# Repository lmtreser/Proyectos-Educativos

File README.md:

# Proyectos Educativos

Proyectos educativos (de diversos origenes) relacionados con trabajos prácticos de las escuelas EEST N°2, EEST N°3 y EEST N°5 de la ciudad de Mar del Plata.

Los diagramas esquemáticos en su mayoría están realizados con Autodesk EAGLE (v7 o superior), y en algunos casos con KiCad (v7 o superior). Mientras que el código generalmente está basado en la API de Arduino.

La ultima versión se puede descargar desde el repositorio [en este enlace](https://github.com/lmtreser/Proyectos).

## Contenidos

- `Analogicas 44` Trabajos "Aplicaciones de Electrónica Analógica I"
- `ArduProfe` Placa entrenadora para Arduino Nano, por el prof. Alejandro Cordero
- `Difusión` Charlas, eventos y difusiones en general
- `Diseño Asistido` Trabajos de diseño de esquemas y PCBs
- `Eduqube` PocketQube educative kit, by [Innova Space](https://www.innova-space.com)
- `Entrenadora Digital` Trabajo práctico "Aplicaciones de Electrónica Digital III"
- `Internet of Things` Trabajos relacionados al IoT
- `Lenguajes Electrónicos` Trabajos "Lenguajes Electrónicos II"
- `Micro Automata` Trabajo práctico "Montaje de Proyectos Electrónicos III"
- `Pulsador de Potencia` Feria de Ciencias, trabajo interdisciplinar, extracurricular
- `Robotec` Competencia de Robótica intercolegial, trabajo interdisciplinar, extracurricular
- `Sensor de Proximidad` Trabajo práctico "Montaje de Proyectos Electrónicos III"

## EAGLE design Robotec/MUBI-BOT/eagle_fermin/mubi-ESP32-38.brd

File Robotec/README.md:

# ROBOTEC

Competencia de Robótica Institucional e Interinstitucional de Escuelas Técnicas de la ciudad de Mar del Plata para alumnos del Ciclo Básico o Superior (Tecnicatura en Electrónica).

[Sitio Web Oficial](https://robotecc.carrd.co/).

## Contenidos del repositorio

- Mubi-Bot es una serie de placas genéricas para la competencia diseñadas por el profesor Fermín Oyarburo de la E.E.S.T. N°5.

- Sigue-Lineas Tercero es un seguidor de lineas que no utiliza microcontrolador. Ideal para su utilización con el Ciclo Básico. Ha sido puesto en marcha con total éxito por el profesor Alfredo Castro de E.E.S.T. N°3.

También se encuentra disponible para su descarga una biblioteca de programación para la API de Arduino, escrita por el profesor Lucas Martín Treser de E.E.S.T. N°3 y E.E.S.T. N°5. La misma permite usar de manera simplificada los componentes más usuales de estos dispositivos. El repositorio se encuentra [aquí](https://github.com/lmtreser/Robotec).

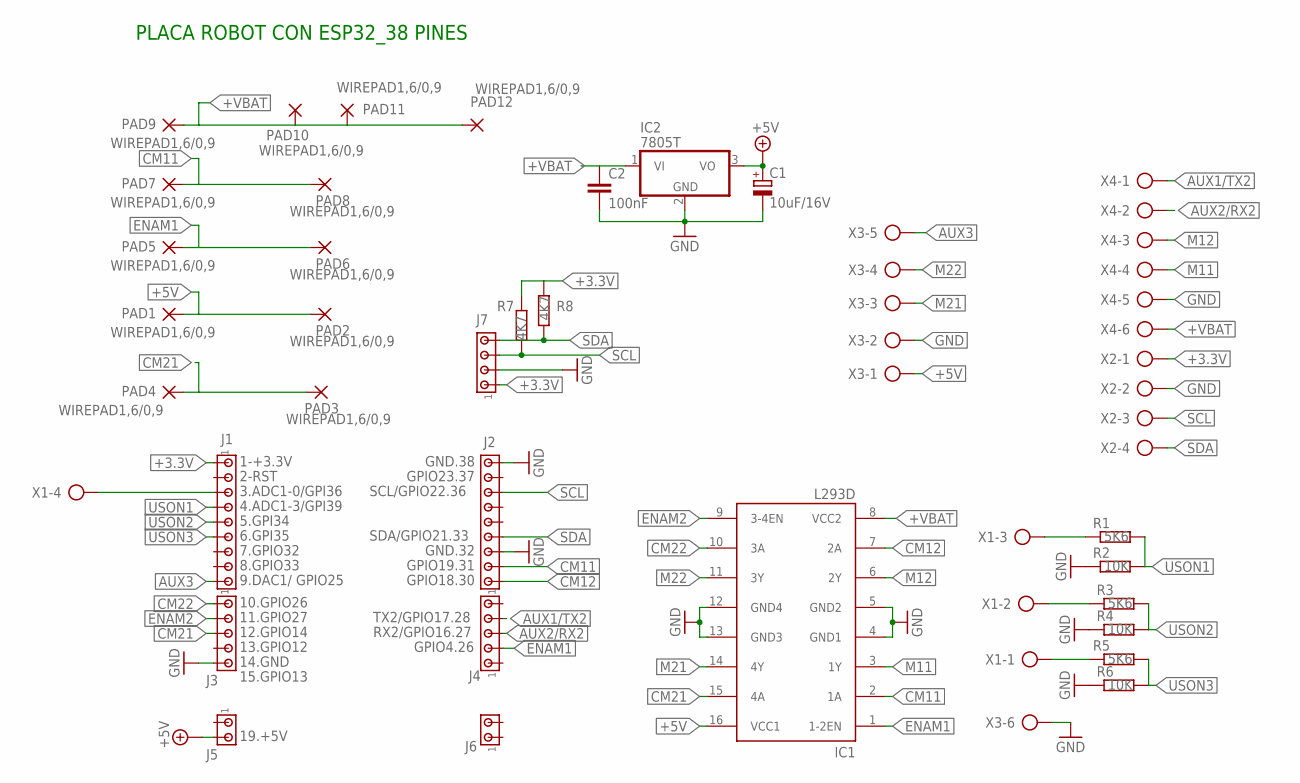
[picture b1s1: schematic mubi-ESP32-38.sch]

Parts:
C1: 10uF/16V; E2,5-6
C2: 100nF; C025-025X050
IC1: L293D; DIL16
IC2: 7805T; TO220H
J1, J2: MTA09-100; 10X09MTA
J3, J4: MTA05-100; 10X05MTA
J5, J6: MTA02-100; 10X02MTA
J7: MTA04-100; 10X04MTA
PAD1, PAD2, PAD3, PAD4, PAD5, PAD6, PAD7, PAD8, PAD9, PAD10, PAD11, PAD12: WIREPAD1,6/0,9; 1,6/0,9
R1, R3, R5: 5K6; 0204/5
R2, R4, R6: 10K; 0204/5
R7, R8: 4K7; 0207/7
X1, X2: AK500/4-H
X3, X4: AK500/6-H

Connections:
+3.3V: J1.1, J7.1, R7.2, R8.2, X2.1
+5V: C1.+, IC1.16 (VCC1), IC2.3 (VO), J5.2, PAD1.1, PAD2.1, X3.1
+VBAT: C2.1, IC1.8 (VCC2), IC2.1 (VI), PAD9.1, PAD10.1, PAD11.1, PAD12.1, X4.6
AUX1/TX2: J4.4, X4.1
AUX2/RX2: J4.3, X4.2
AUX3: J1.9, X3.5
CM11: IC1.2 (1A), J2.2, PAD7.1, PAD8.1
CM12: IC1.7 (2A), J2.1
CM21: IC1.15 (4A), J3.3, PAD3.1, PAD4.1
CM22: IC1.10 (3A), J3.1
ENAM1: IC1.1 (1-2EN), J4.2, PAD5.1, PAD6.1
ENAM2: IC1.9 (3-4EN), J3.2
GND: C1.-, C2.2, IC1.4 (GND1), IC1.5 (GND2), IC1.12 (GND4), IC1.13 (GND3), IC2.2 (GND), J2.3, J2.9, J3.5, J7.2, R2.1, R4.1, R6.1, X2.2, X3.2, X3.6, X4.5
M11: IC1.3 (1Y), X4.4
M12: IC1.6 (2Y), X4.3
M21: IC1.14 (4Y), X3.3
M22: IC1.11 (3Y), X3.4
unnamed: R1.1, X1.3
unnamed: R3.1, X1.2
unnamed: R5.1, X1.1
unnamed: J1.3, X1.4
SCL: J2.7, J7.3, R7.1, X2.3
SDA: J2.4, J7.4, R8.1, X2.4
USON1: J1.4, R1.2, R2.2
USON2: J1.5, R3.2, R4.2
USON3: J1.6, R5.2, R6.2

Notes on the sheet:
1-+3.3V
2-RST
3.ADC1-0/GPI36
4.ADC1-3/GPI39
5.GPI34
6.GPI35
7.GPIO32
8.GPIO33
9.DAC1/ GPIO25
10.GPIO26
11.GPIO27
12.GPIO14
14.GND
15.GPIO13
19.+5V
GND.38
GPIO23.37
SCL/GPIO22.36
SDA/GPIO21.33
GND.32
GPIO19.31
GPIO18.30
TX2/GPIO17.28
RX2/GPIO16.27
GPIO4.26
PLACA ROBOT CON ESP32_38 PINES
13.GPIO12

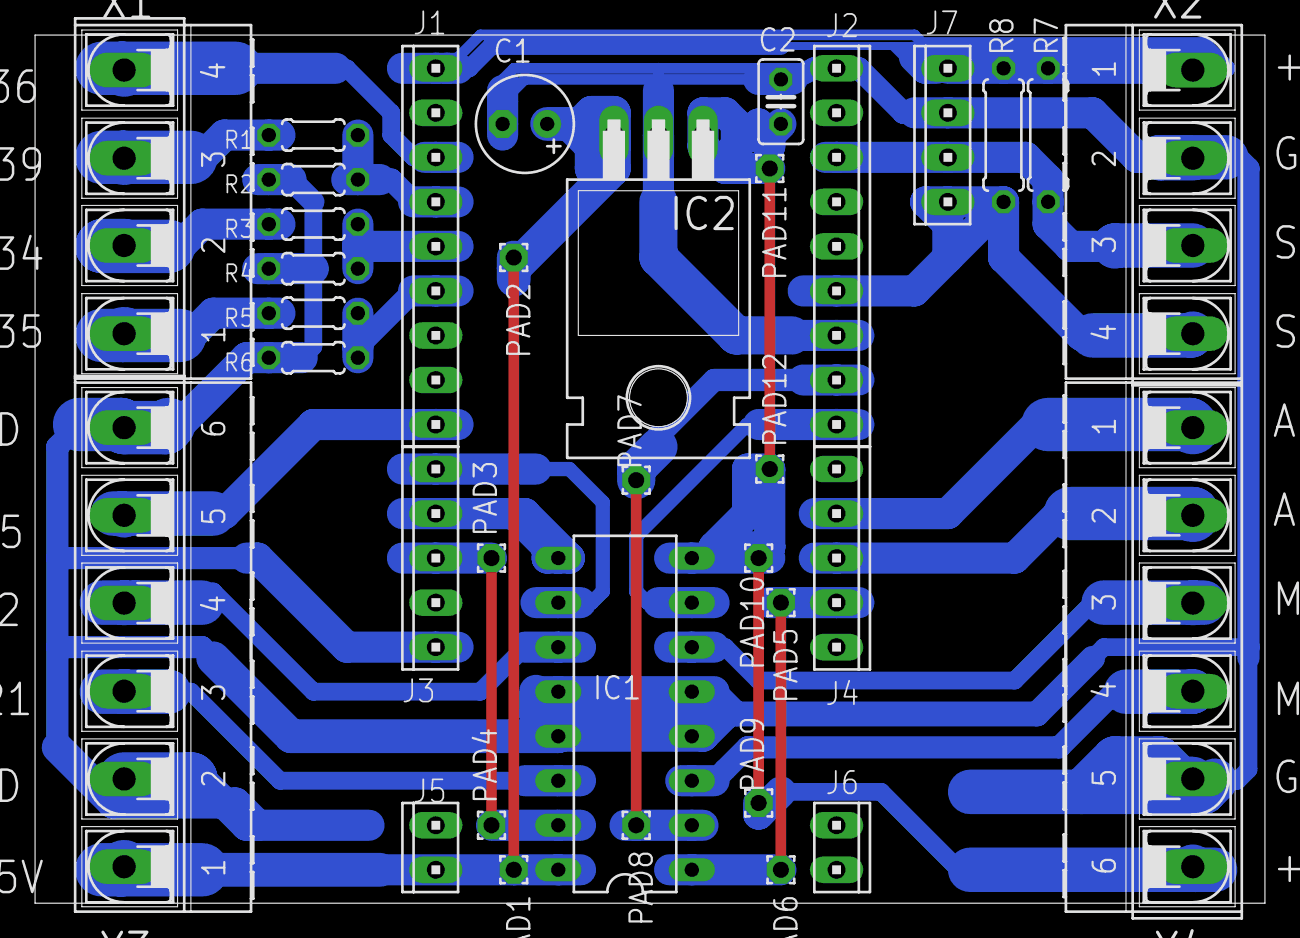
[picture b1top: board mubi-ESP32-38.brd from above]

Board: 2 copper layers, 70.2 x 49.5 mm, 35 parts (0 on the bottom side), 26 nets.

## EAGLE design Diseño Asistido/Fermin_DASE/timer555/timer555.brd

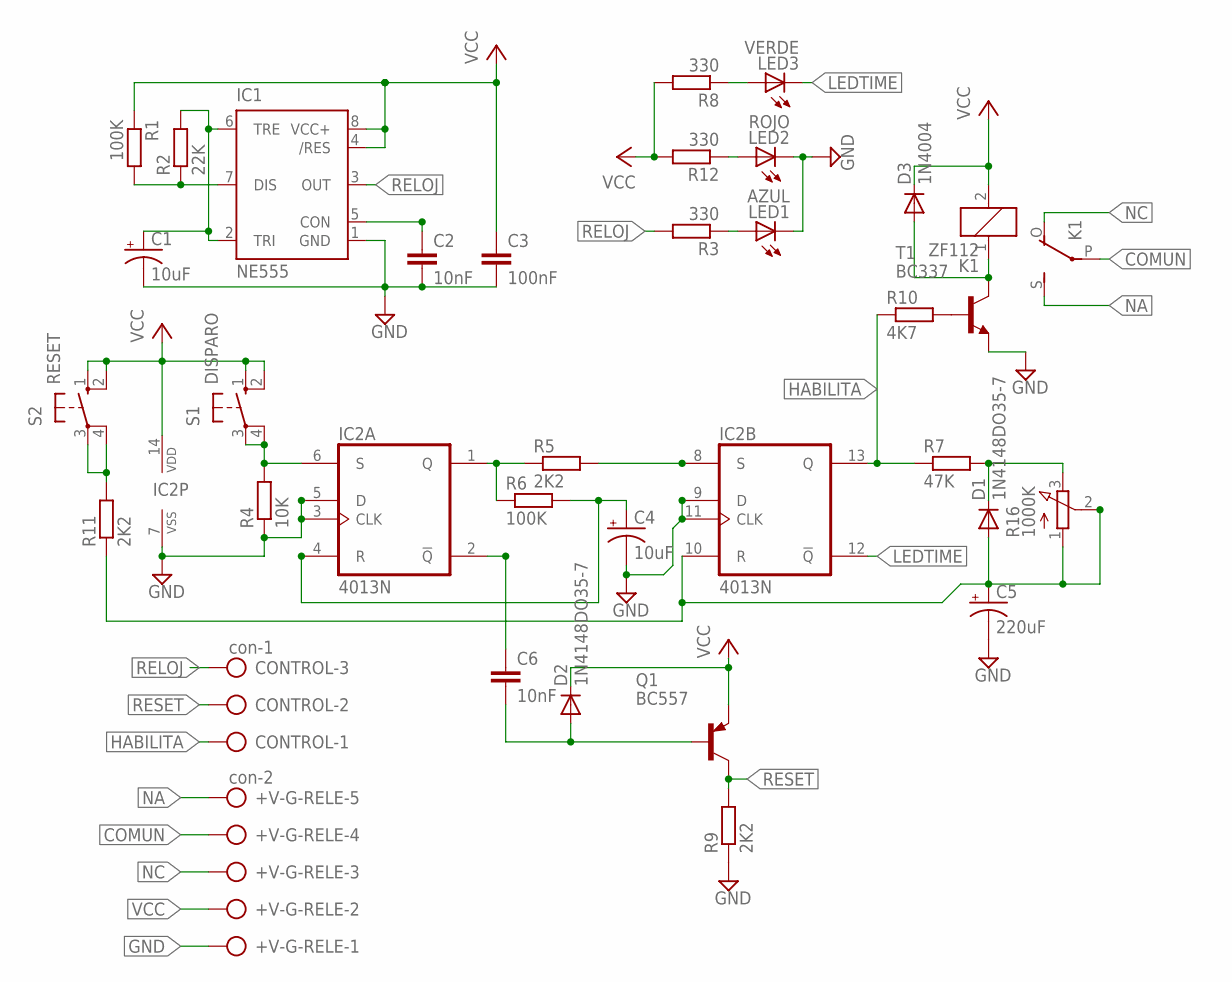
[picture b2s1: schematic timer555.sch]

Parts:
+V-G-RELE: con-2; AK500/5
C1, C4: 10uF; E2,5-5
C2, C6: 10nF; C050-025X075
C3: 100nF; C050-025X075
C5: 220uF; E3,5-8
CONTROL: con-1; AK500/3
D1, D2: 1N4148DO35-7; DO35-7
D3: 1N4004; DO41-10
IC1: NE555; DIL-08
IC2: 4013N; DIL14
K1: ZF112
LED1: AZUL; LED3MM
LED2: ROJO; LED3MM
LED3: VERDE; LED3MM
Q1: BC557; TO92-EBC
R1, R6: 100K; 0207/7
R2: 22K; 0207/7
R3, R8, R12: 330; 0207/7
R4: 10K; 0207/7
R5, R9, R11: 2K2; 0207/7
R7: 47K; 0207/7
R10: 4K7; 0207/7
R16: 1000K; 3RP/1610N
S1: DISPARO; B3F-10XX
S2: RESET; B3F-10XX
T1: BC337; TO92

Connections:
COMUN: +V-G-RELE.4, K1.P; also elsewhere on the board
GND: +V-G-RELE.1, C1.-, C2.2, C3.2, C4.-, C5.-, IC1.1 (GND), IC2.3 (CLK), IC2.5 (D), IC2.7 (VSS), IC2.9 (D), IC2.11 (CLK), LED1.K (C), LED2.K (C), R4.1, R9.1, T1.1 (E); also elsewhere on the board
HABILITA: CONTROL.1, IC2.13 (Q), R7.1, R10.1; also elsewhere on the board
LEDTIME: IC2.12 (!Q), LED3.K (C)
unnamed: D3.A, K1.1, T1.3 (C)
unnamed: IC2.1 (Q), R5.1, R6.1
unnamed: C1.+, IC1.2 (TRI), IC1.6 (TRE), R2.2
unnamed: C4.+, IC2.4 (R), R6.2
unnamed: IC1.7 (DIS), R1.2, R2.1
unnamed: C2.1, IC1.5 (CON)
unnamed: D1.C, R7.2, R16.3 (E)
unnamed: LED3.A, R8.1
unnamed: LED1.A, R3.1
unnamed: IC2.6 (S), R4.2, S1.3, S1.4 (P1)
unnamed: C5.+, D1.A, IC2.10 (R), R11.1, R16.1 (A), R16.2 (S)
unnamed: R11.2, S2.3, S2.4 (P1)
unnamed: LED2.A, R12.1
unnamed: R10.2, T1.2 (B)
unnamed: C6.1, IC2.2 (!Q)
unnamed: C6.2, D2.A, Q1.B
NA: +V-G-RELE.5, K1.S; also elsewhere on the board
RELOJ: CONTROL.3, IC1.3 (OUT), R3.2; also elsewhere on the board
RESET: CONTROL.2, Q1.C, R9.2; also elsewhere on the board
S$3: +V-G-RELE.3, K1.O
SET2: IC2.8 (S), R5.2
VCC: +V-G-RELE.2, C3.1, D2.C, D3.C, IC1.4 (/RES), IC1.8 (VCC+), IC2.14 (VDD), K1.2, Q1.E, R1.1, R8.2, R12.2, S1.1 (S), S1.2 (S1), S2.1 (S), S2.2 (S1); also elsewhere on the board

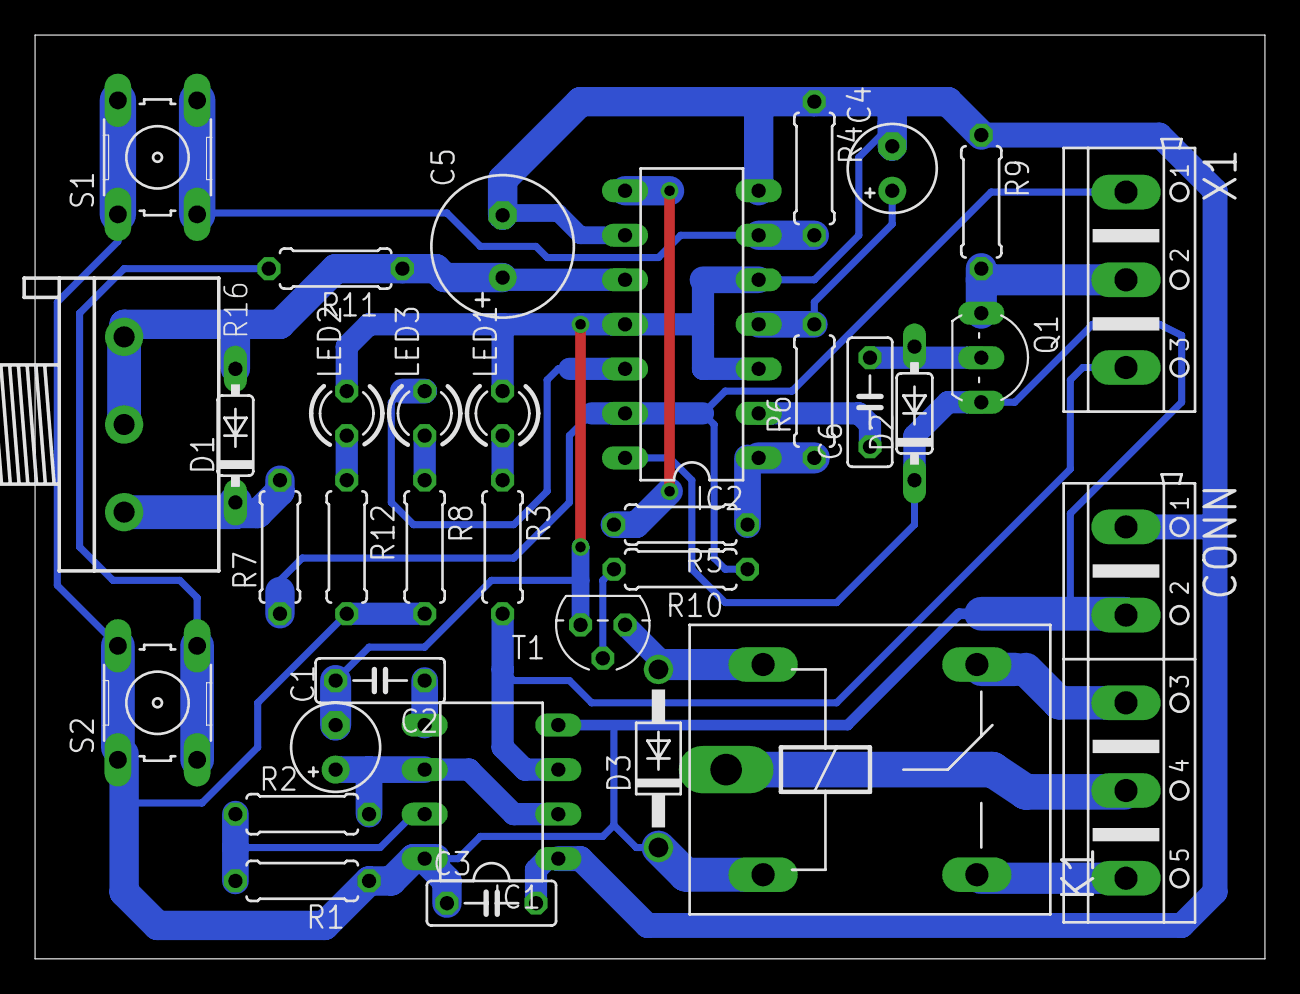
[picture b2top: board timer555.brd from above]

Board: 2 copper layers, 70.2 x 52.7 mm, 34 parts (0 on the bottom side), 25 nets.

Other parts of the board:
CONN: AK500/5
X1: AK500/3

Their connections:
COMUN: CONN.4; also elsewhere on the board
GND: CONN.1; also elsewhere on the board
HABILITA: X1.1; also elsewhere on the board
NA: CONN.5; also elsewhere on the board
RELOJ: X1.3; also elsewhere on the board
RESET: X1.2; also elsewhere on the board
VCC: CONN.2; also elsewhere on the board

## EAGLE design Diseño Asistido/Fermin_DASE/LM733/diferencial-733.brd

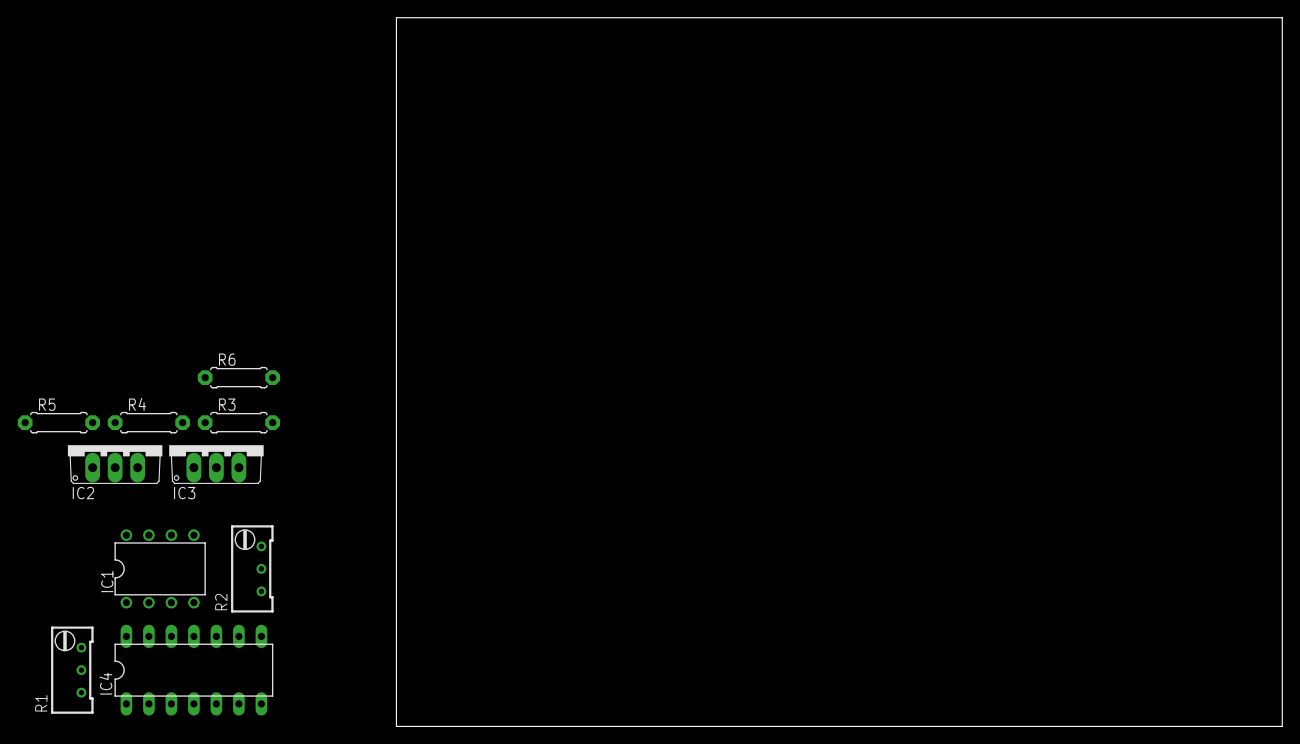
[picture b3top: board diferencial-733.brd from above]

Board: 2 copper layers, 100.0 x 80.0 mm, 10 parts (0 on the bottom side), 3 nets, no tracks yet.

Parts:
IC1: LM555N; DIL08
IC2: 7805TV; TO220V
IC3: MC79M15BT; TO220V
IC4: 7400N; DIL14
R1, R2: RTRIM64W
R3, R4, R5, R6: 0207/7

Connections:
GND: IC1.1, R4.1, R5.1
unnamed: IC4.14, R4.2
unnamed: IC4.7, R5.2

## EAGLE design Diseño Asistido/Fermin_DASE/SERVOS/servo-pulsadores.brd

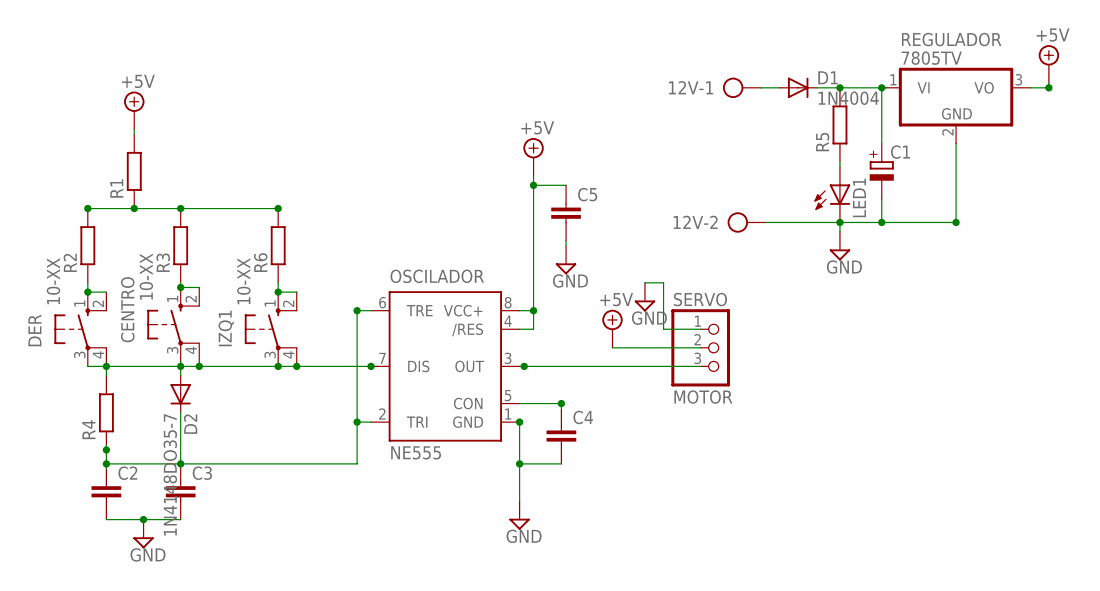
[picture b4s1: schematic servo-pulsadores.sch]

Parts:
12V: AK500/2
C1: CPOL-EUE2.5-7; E2,5-7
C2, C3, C4: C-EU025-025X050; C025-025X050
C5: C-EU050-025X075; C050-025X075
CENTRO: 10-XX; B3F-10XX
D1: 1N4004; DO41-10
D2: 1N4148DO35-7; DO35-7
DER: 10-XX; B3F-10XX
IZQ1: 10-XX; B3F-10XX
LED1: LED3MM
OSCILADOR: NE555; DIL-08
R1, R2, R3, R4, R5, R6: R-EU_0207/7; 0207/7
REGULADOR: 7805TV; TO220V
SERVO: MOTOR; 1X03

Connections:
+5V: C5.1, OSCILADOR.4 (/RES), OSCILADOR.8 (VCC+), R1.2, REGULADOR.3 (VO), SERVO.2
GND: 12V.2, C1.-, C2.2, C3.2, C4.2, C5.2, LED1.K (C), OSCILADOR.1 (GND), REGULADOR.2 (GND), SERVO.1
unnamed: LED1.A, R5.1
unnamed: DER.1 (S), DER.2 (S1), R2.1
unnamed: OSCILADOR.3 (OUT), SERVO.3
unnamed: CENTRO.1 (S), CENTRO.2 (S1), R3.1
unnamed: R1.1, R2.2, R3.2, R6.2
unnamed: C4.1, OSCILADOR.5 (CON)
unnamed: C2.1, C3.1, D2.C, OSCILADOR.2 (TRI), OSCILADOR.6 (TRE), R4.1
unnamed: IZQ1.1 (S), IZQ1.2 (S1), R6.1
unnamed: CENTRO.3, CENTRO.4 (P1), D2.A, DER.3, DER.4 (P1), IZQ1.3, IZQ1.4 (P1), OSCILADOR.7 (DIS), R4.2
unnamed: C1.+, D1.C, R5.2, REGULADOR.1 (VI)
unnamed: 12V.1, D1.A

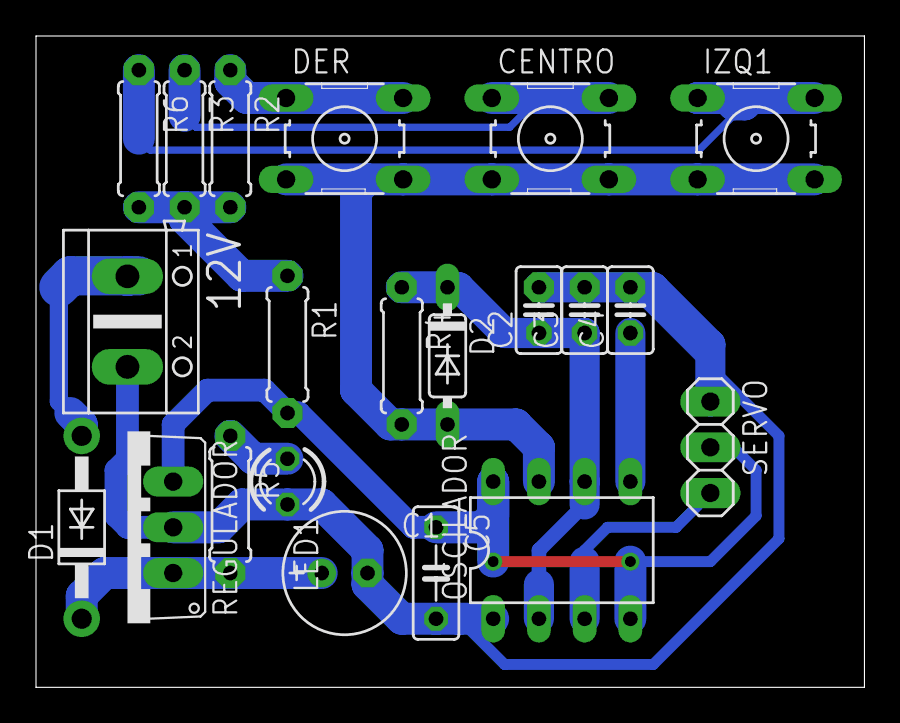
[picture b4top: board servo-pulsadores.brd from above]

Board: 2 copper layers, 46.0 x 36.2 mm, 21 parts (0 on the bottom side), 13 nets.

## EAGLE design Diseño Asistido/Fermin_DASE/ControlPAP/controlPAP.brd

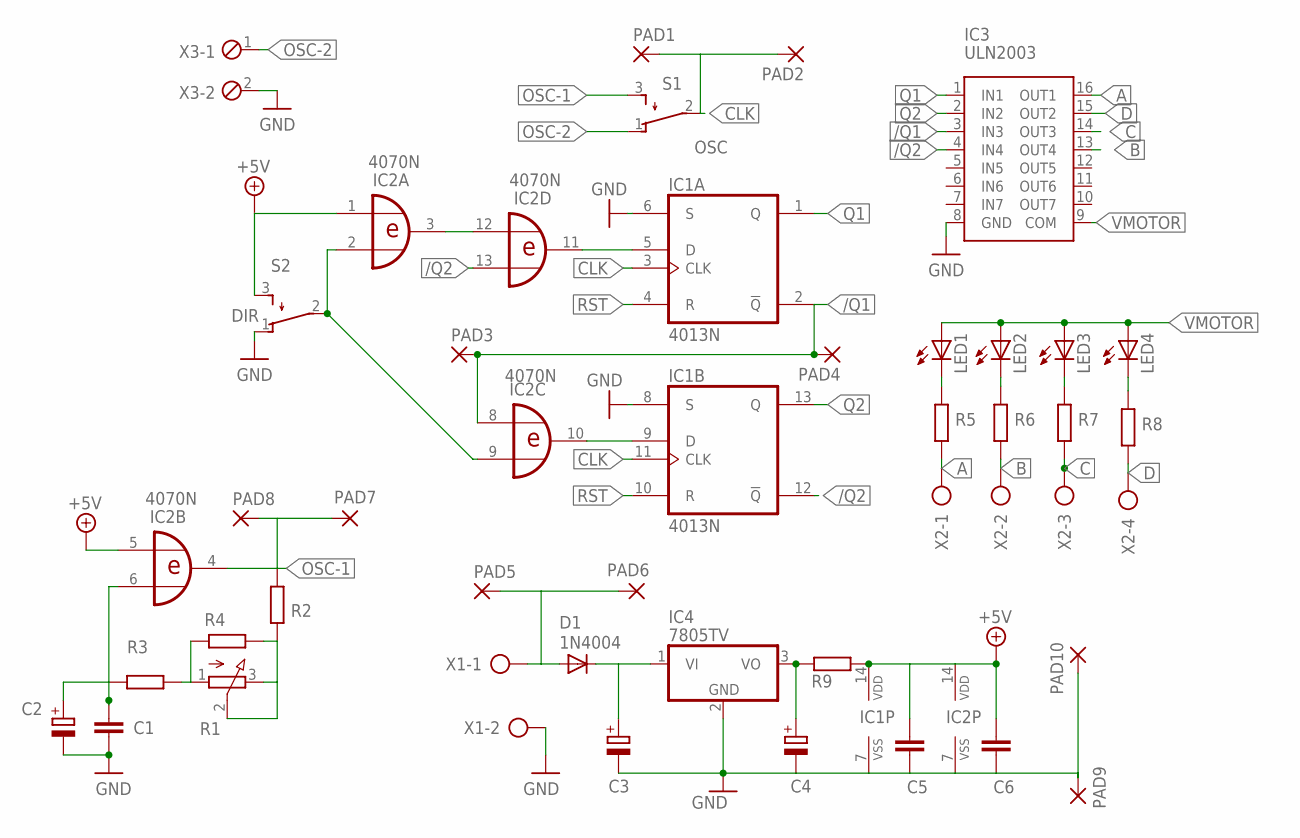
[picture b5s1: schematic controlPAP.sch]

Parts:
C1, C5, C6: C-EU050-025X075; C050-025X075
C2, C4: CPOL-EUE2.5-5; E2,5-5
C3: CPOL-EUE2.5-7; E2,5-7
D1: 1N4004; DO41-10
IC1: 4013N; DIL14
IC2: 4070N; DIL14
IC3: ULN2003; DIP16
IC4: 7805TV; TO220V
LED1, LED2, LED3, LED4: LED3MM; LED_3MM
PAD1, PAD2, PAD3, PAD4, PAD5, PAD6, PAD7, PAD8, PAD9, PAD10: 1,6/0,9
R1: 3RP/1610N
R2, R3, R4, R5, R6, R7, R8: R-EU_0207/7; 0207/7
R9: R-EU_0207/12; 0207/12
S1: OSC; TL3XPO
S2: DIR; TL3XPO
X1: AK500/2
X2: AK500/4
X3: MPT2; 2POL254

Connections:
+5V: C5.1, C6.1, IC1.14 (VDD), IC2.14 (VDD), R9.2
+12V: IC2.1 (I0), IC2.5 (I0), S2.3 (S)
/Q1: IC1.2 (!Q), IC2.8 (I0), IC3.3 (IN3), PAD3.1, PAD4.1
/Q2: IC1.12 (!Q), IC2.13 (I1), IC3.4 (IN4)
A: IC3.16 (OUT1), R5.2, X2.1
B: IC3.13 (OUT4), R6.2, X2.2
C: IC3.14 (OUT3), R7.2, X2.3
CLK: IC1.3 (CLK), IC1.11 (CLK), PAD1.1, PAD2.1, S1.2
D: IC3.15 (OUT2), R8.2, X2.4
GND: C1.2, C2.-, C3.-, C4.-, C5.2, C6.2, IC1.6 (S), IC1.7 (VSS), IC1.8 (S), IC2.7 (VSS), IC3.8 (GND), IC4.2 (GND), PAD9.1, PAD10.1, S2.1 (O), X1.2, X3.2
unnamed: IC1.5 (D), IC2.11 (O)
unnamed: IC2.2 (I1), IC2.9 (I1), S2.2
unnamed: IC2.3 (O), IC2.12 (I0)
unnamed: D1.A, PAD5.1, PAD6.1, X1.1
unnamed: R1.1 (A), R3.2, R4.1
unnamed: LED1.K (C), R5.1
unnamed: R1.2 (S), R1.3 (E), R2.2, R4.2
unnamed: C3.+, D1.C, IC4.1 (VI)
unnamed: LED2.K (C), R6.1
unnamed: C1.1, C2.+, IC2.6 (I1), R3.1
unnamed: LED3.K (C), R7.1
unnamed: LED4.K (C), R8.1
unnamed: C4.+, IC4.3 (VO), R9.1
unnamed: IC1.9 (D), IC2.10 (O)
OSC-1: IC2.4 (O), PAD7.1, PAD8.1, R2.1, S1.3 (S)
OSC-2: S1.1 (O), X3.1
Q1: IC1.1 (Q), IC3.1 (IN1)
Q2: IC1.13 (Q), IC3.2 (IN2)
RST: IC1.4 (R), IC1.10 (R)
VMOTOR: IC3.9 (COM), LED1.A, LED2.A, LED3.A, LED4.A

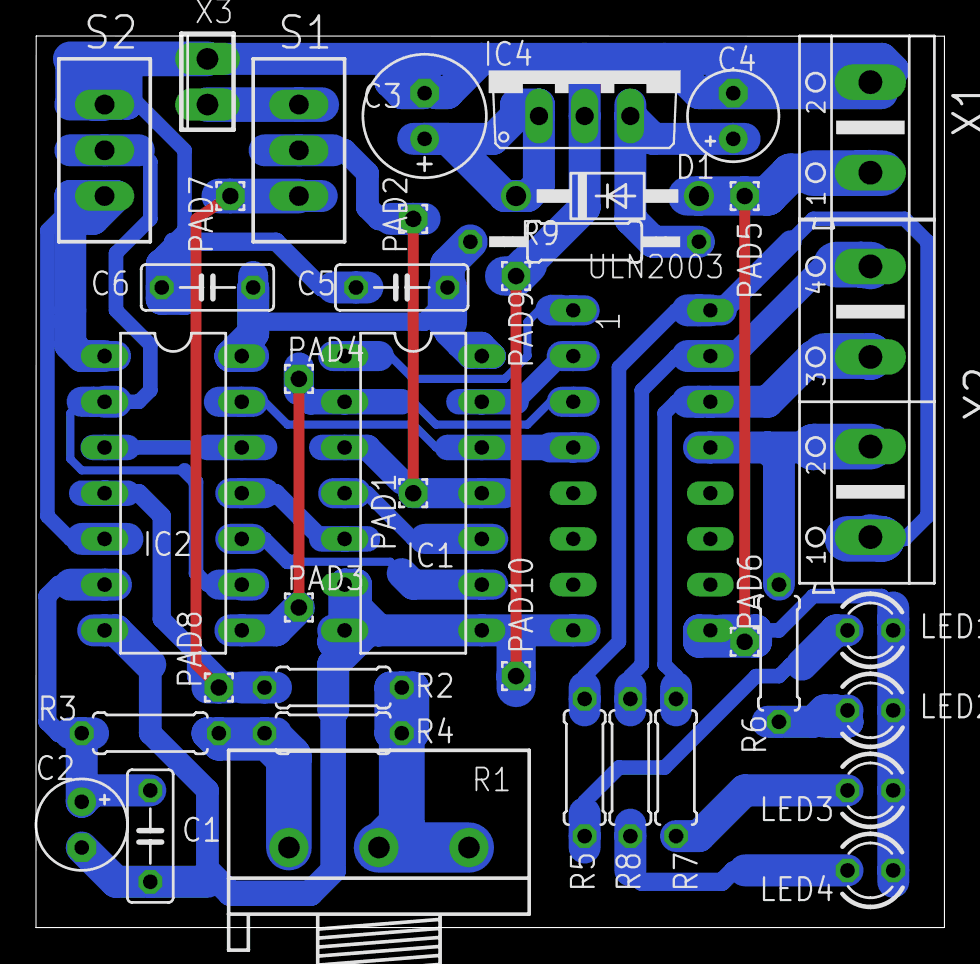
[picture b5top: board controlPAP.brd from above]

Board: 2 copper layers, 50.5 x 49.5 mm, 39 parts (0 on the bottom side), 30 nets.

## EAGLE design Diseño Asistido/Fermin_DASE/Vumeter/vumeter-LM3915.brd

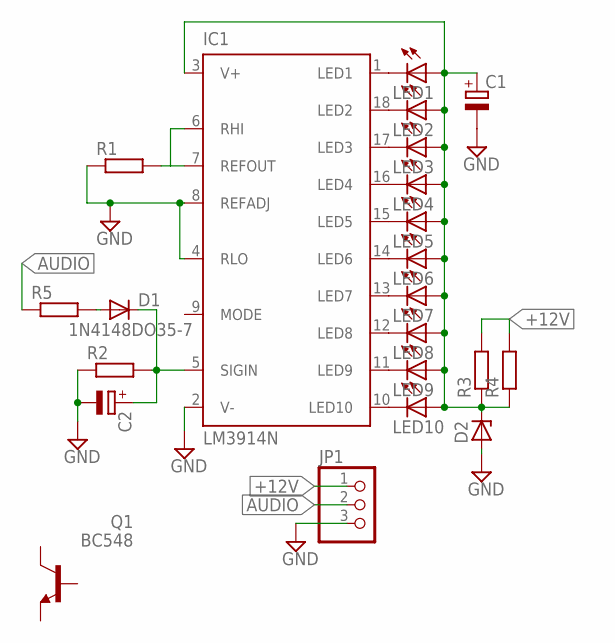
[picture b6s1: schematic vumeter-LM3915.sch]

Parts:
C1, C2: CPOL-EUE2-4; E2-4
D1: 1N4148DO35-7; DO35-7
D2: ZENER-DIODEZD-10; ZDIO-10
IC1: LM3914N; DIL18
JP1: PINHD-1X3; 1X03
LED1, LED2, LED3, LED4, LED5, LED6, LED7, LED8, LED9, LED10: LED3MM
Q1: BC548; TO92-EBC
R1, R2, R3, R4, R5: R-EU_0207/7; 0207/7

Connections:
+12V: JP1.1, R3.2, R4.2
AUDIO: JP1.2, R5.1
GND: C1.-, C2.-, D2.A, IC1.2 (V-), IC1.4 (RLO), IC1.8 (REFADJ), JP1.3, R1.1, R2.1
unnamed: IC1.1 (LED1), LED1.K (C)
unnamed: IC1.18 (LED2), LED2.K (C)
unnamed: IC1.17 (LED3), LED3.K (C)
unnamed: IC1.16 (LED4), LED4.K (C)
unnamed: IC1.15 (LED5), LED5.K (C)
unnamed: IC1.14 (LED6), LED6.K (C)
unnamed: IC1.13 (LED7), LED7.K (C)
unnamed: IC1.11 (LED9), LED9.K (C)
unnamed: IC1.10 (LED10), LED10.K (C)
unnamed: IC1.6 (RHI), IC1.7 (REFOUT), R1.2
unnamed: C2.+, D1.C, IC1.5 (SIGIN), R2.2
unnamed: D1.A, R5.2
unnamed: C1.+, D2.C, IC1.3 (V+), LED1.A, LED2.A, LED3.A, LED4.A, LED5.A, LED6.A, LED7.A, LED8.A, LED9.A, LED10.A, R3.1, R4.1
unnamed: IC1.12 (LED8), LED8.K (C)

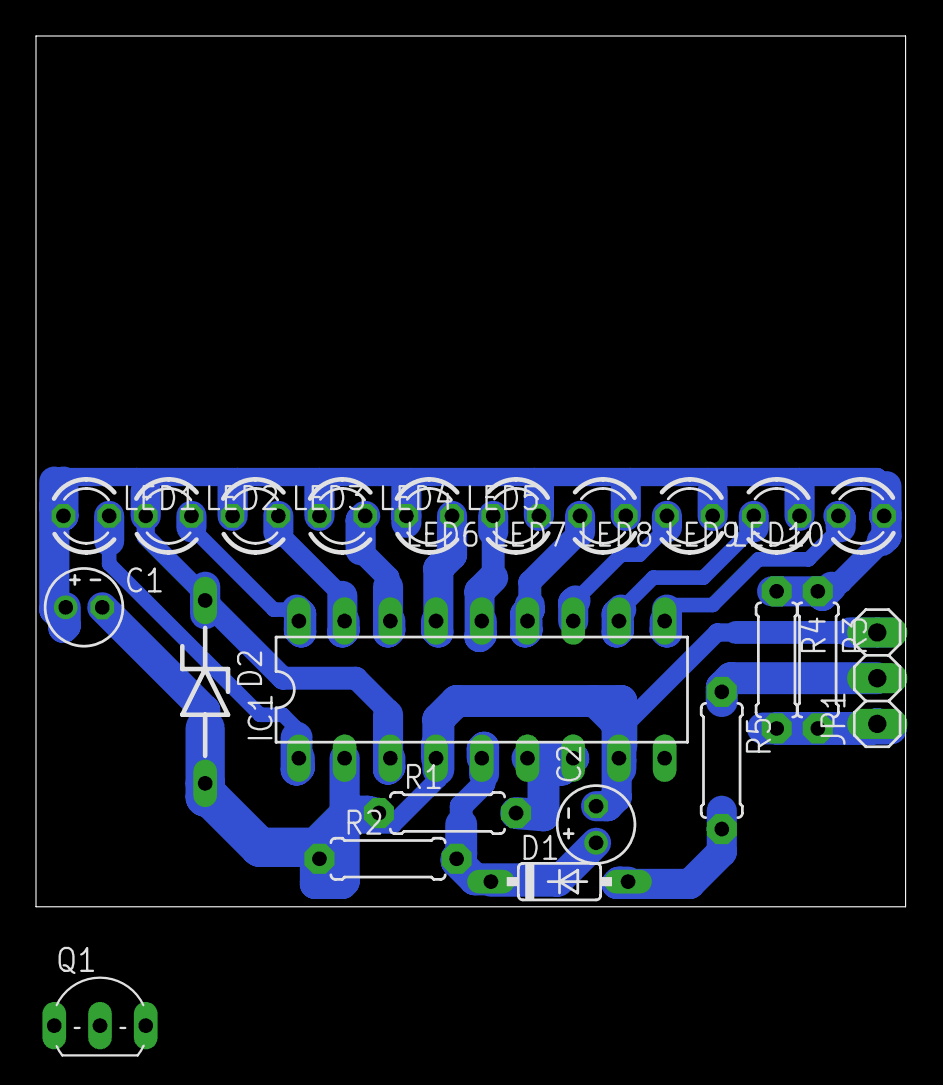
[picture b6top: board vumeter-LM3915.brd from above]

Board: 2 copper layers, 48.3 x 48.4 mm, 22 parts (0 on the bottom side), 17 nets.

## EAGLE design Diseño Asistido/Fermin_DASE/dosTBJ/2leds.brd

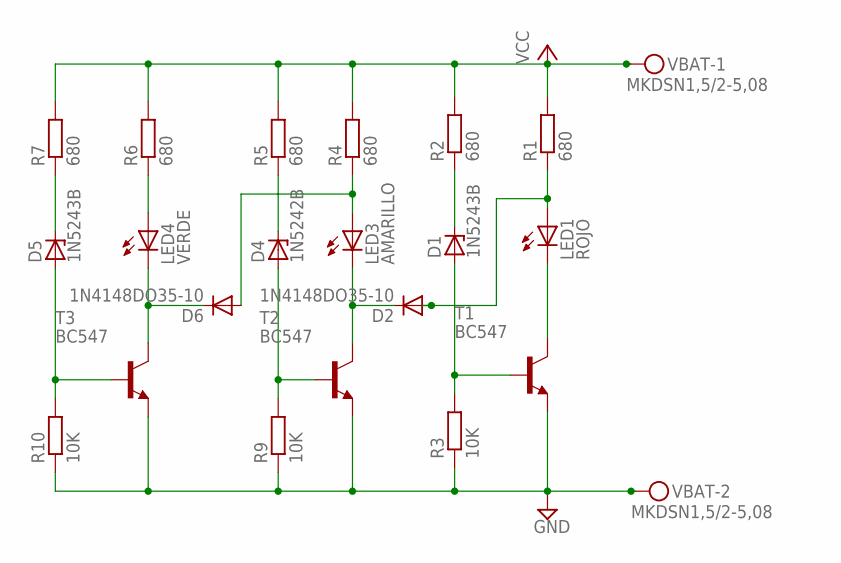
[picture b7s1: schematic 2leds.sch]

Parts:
D1, D5: 1N5243B; DO35Z10
D2, D6: 1N4148DO35-10; DO35-10
D4: 1N5242B; DO35Z10
LED1: ROJO; LED3MM
LED3: AMARILLO; LED3MM
LED4: VERDE; LED3MM
R1, R2, R4, R5, R6, R7: 680; 0207/10
R3, R9, R10: 10K; 0207/10
T1, T2, T3: BC547; TO92
VBAT: MKDSN1,5/2-5,08

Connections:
GND: R3.1, R9.1, R10.1, T1.1 (E), T2.1 (E), T3.1 (E), VBAT.2
unnamed: D1.A, R3.2, T1.2 (B)
unnamed: LED1.K (C), T1.3 (C)
unnamed: D5.A, R10.2, T3.2 (B)
unnamed: D4.A, R9.2, T2.2 (B)
unnamed: D2.A, LED1.A, R1.1
unnamed: D2.C, LED3.K (C), T2.3 (C)
unnamed: D6.A, LED3.A, R4.1
unnamed: D4.C, R5.1
unnamed: D1.C, R2.1
unnamed: D6.C, LED4.K (C), T3.3 (C)
unnamed: LED4.A, R6.1
unnamed: D5.C, R7.1
VCC: R1.2, R2.2, R4.2, R5.2, R6.2, R7.2, VBAT.1

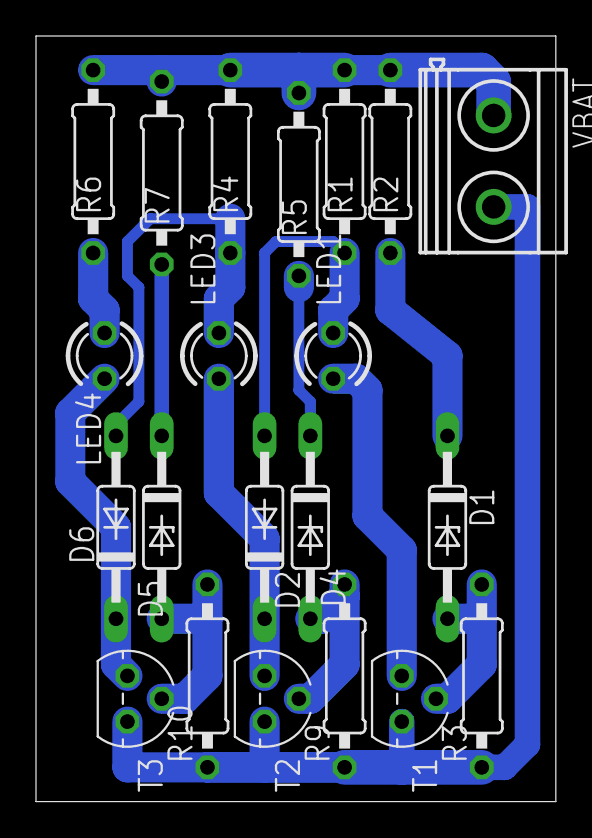
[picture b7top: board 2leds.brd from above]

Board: 2 copper layers, 28.9 x 42.5 mm, 21 parts (0 on the bottom side), 14 nets.

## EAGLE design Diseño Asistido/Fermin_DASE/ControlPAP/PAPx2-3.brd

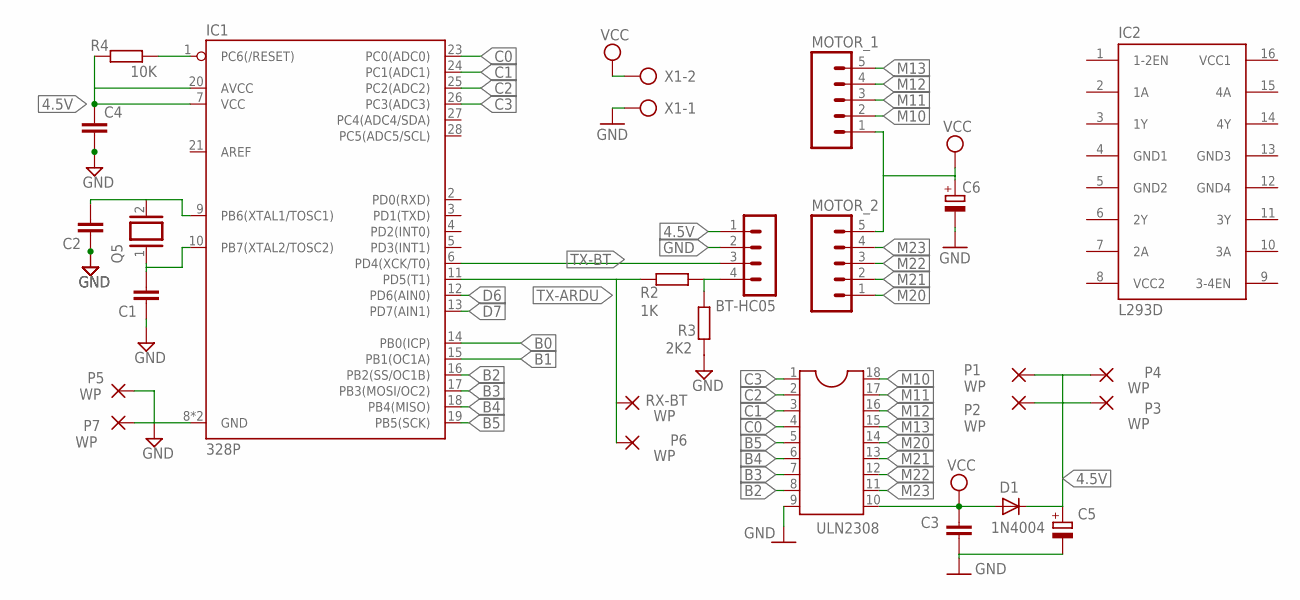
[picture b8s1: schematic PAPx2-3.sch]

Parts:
BT-HC05: MA04-1
C1, C2: C-EU025-025X050; C025-025X050
C3, C4: C-EU050-025X075; C050-025X075
C5, C6: CPOL-EUE2.5-5; E2,5-5
D1: 1N4004; DO41-10
IC1: 328P; DIP28
IC2: L293D; DIL16
MOTOR_1, MOTOR_2: M05; 05P
P1, P2, P3, P4, P5, P6, P7: WP; 1,6/0,8
Q5: XTAL/S; QS
R2: 1K; 0204/7
R3: 2K2; 0204/7
R4: 10K; 0204/7
RX-BT: WP; 1,6/0,8
ULN2308: DIL18
X1: AK500/2

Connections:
4.5V: BT-HC05.1, C4.1, C5.+, D1.C, IC1.7 (VCC), IC1.20 (AVCC), P1.1, P2.1, P3.1, P4.1, R4.1
B0: IC1.14 (PB0(ICP))
B1: IC1.15 (PB1(OC1A))
B2: IC1.16 (PB2(SS/OC1B)), ULN2308.8
B3: IC1.17 (PB3(MOSI/OC2)), ULN2308.7
B4: IC1.18 (PB4(MISO)), ULN2308.6
B5: IC1.19 (PB5(SCK)), ULN2308.5
C0: IC1.23 (PC0(ADC0)), ULN2308.4
C1: IC1.24 (PC1(ADC1)), ULN2308.3
C2: IC1.25 (PC2(ADC2)), ULN2308.2
C3: IC1.26 (PC3(ADC3)), ULN2308.1
D6: IC1.12 (PD6(AIN0))
D7: IC1.13 (PD7(AIN1))
GND: BT-HC05.2, C1.1, C2.1, C3.2, C4.2, C5.-, C6.-, IC1.8 (GND), IC1.22 (GND), P5.1, P7.1, R3.1, ULN2308.9, X1.1
GND1: IC2.4 (GND1)
GND2: IC2.5 (GND2)
GND3: IC2.13 (GND3)
GND4: IC2.12 (GND4)
M10: MOTOR_1.2, ULN2308.18
M11: MOTOR_1.3, ULN2308.17
M12: MOTOR_1.4, ULN2308.16
M13: MOTOR_1.5, ULN2308.15
M20: MOTOR_2.1, ULN2308.14
M21: MOTOR_2.2, ULN2308.13
M22: MOTOR_2.3, ULN2308.12
M23: MOTOR_2.4, ULN2308.11
unnamed: BT-HC05.4, R2.2, R3.2
unnamed: C1.2, IC1.10 (PB7(XTAL2/TOSC2)), Q5.1
unnamed: C2.2, IC1.9 (PB6(XTAL1/TOSC1)), Q5.2
unnamed: IC1.1 (PC6(/RESET)), R4.2
TX-ARDU: IC1.11 (PD5(T1)), P6.1, R2.1, RX-BT.1
TX-BT: BT-HC05.3, IC1.6 (PD4(XCK/T0))
VCC: C3.1, C6.+, D1.A, MOTOR_1.1, MOTOR_2.5, ULN2308.10, X1.2
VCC1: IC2.16 (VCC1)
VCC2: IC2.8 (VCC2)

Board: 2 copper layers, 26 parts (0 on the bottom side), 25 nets, no tracks yet.

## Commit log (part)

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2023-12-02 Micro Automata con Arduino
2023-12-02 Actualizado README
2023-12-02 Sensor de proximidad IR
2023-12-02 Robotec Sigue-Lineas EEST N°3
2023-12-02 Competencia de Robótica
2023-12-02 Firmware Arduino para test de hardware
2023-12-02 Placa Mubi-Bot / Prof. Oyarburo
2023-12-02 Eliminado de archivos innecesarios
2023-12-02 Sigue-Lineas E.E.S.T. N°3
2023-12-02 Vúmetro con Arduino
2023-12-02 Firmware para pruebas
2023-12-02 Placa de desarrollo ESP32 Neon UNMdP FI
2023-12-02 Relé WiFi con ESP-01
2023-12-02 Pulsador de Potencia E.E.E. N°513
2023-12-02 Entrenadora Digital
2023-12-02 Amplificador 8W con TDA2003
2023-12-02 Internet de las cosas
2023-12-02 Robot Sigue-Lineas Ciclo Básico
2023-12-02 Amplificador 8W EEST N°2
2023-12-02 Vumetro con Arduino EEST N°2
2023-12-02 Actualización de archivos
2023-12-02 Diagrama esquemático
2023-12-04 Entrenadora Digital con Arduino
2023-12-04 Pulsador de Potencia
2023-12-06 Lista de materiales
2023-12-08 STL gabinete
2023-12-28 Actualización readme
2023-12-28 Documentación
2023-12-28 Reglamento Sumo v2022
2023-12-28 Reglamento Carreras v2022
2023-12-28 Reglamento Laberintos v2022
2023-12-28 Sugerencias JL Bruni
2024-02-01 update docs
2024-02-01 add src js Clicker
2024-02-03 update Project Neon UNMdP FI
2024-02-06 Actualizar README.md
2024-02-06 add dase
2024-02-21 Amplificador de auriculares
2024-02-21 Entrenadora PICAXE-08
2024-02-21 Control de velocidad para motor DC
2024-02-21 Acondicionador para caudalimetro
2024-02-21 Divisor de frecuencia
2024-02-21 Sistema con PICmicro para máquina Vortex
2024-02-21 PedalPhone
2024-02-21 Datalogger
2024-02-21 ArduiMini
2024-02-21 Adaptador ZIF
2024-02-21 Coron DS7 Clone
2024-03-05 add charla perfil de un tecnico
2024-03-07 add ArduProfe
2024-03-07 add Innova Space Eduqube
2024-03-12 update entrenadora digital
2024-03-18 add Sensor de temperatura
2024-03-26 update MUBI-BOT
2024-05-07 add modulo rele
2024-05-07 update sensor temperatura
2024-05-16 add datalogger
2024-05-16 add wokwi files
2024-05-16 add arduino sketch
2024-05-16 add arduino binaries
2024-05-16 add simulacion (SimulIDE-1.0.0-SR2 R1449)
2024-05-17 add Vení a la Técnica
2024-06-05 update datalogger
2024-07-31 update sch & brd
2024-08-09 update dirs
2024-08-09 add motor pap driver
2024-08-16 add dispositivo domotico
2024-08-16 add ino file
2024-09-06 add firmware modbus rtu
2024-09-13 add driver tester servos
2024-09-14 add 555 inventable
2024-09-19 add ntc table
2024-09-26 add esp32 wiring
2024-09-27 add mqtt example
2024-10-03 update modbusrtu
2024-10-07 update objects visibility
2024-10-07 add Eyes
2025-01-23 add Maze-Solving-Algorithms-Comparison
2025-02-14 add robot diferencial pdf
2025-03-25 add control motor DC
2025-03-25 add robot laberintos
2025-03-25 add algorithms
2025-04-01 modified chassis
2025-04-01 add fermin dase projects
2025-04-04 add algoritmo llenado
2025-04-22 update eagle project
2025-05-16 add Control Remoto
2025-05-16 fix buttons
2025-05-16 fix ui, buttons
2025-05-21 add analogico.html
2025-05-23 update html
2025-06-12 update htmls
2025-06-12 update analogico
2025-06-12 update gap
2025-06-30 add docs
2025-07-01 add micromouse robot
2025-07-05 add tabla comparativa
2025-07-09 update modulo rele
2025-07-10 add chassis labe v1
2025-07-10 update chassis
2025-07-15 update robot labe
2025-07-16 sch/pcb eagle fermin
2025-07-16 update 3d model
2025-07-16 mubi-bot3 v4, kicad project (legacy)
2025-07-16 update sch pcb kicad v9
2025-07-19 update sch & pcb
2025-07-19 add img 3d
2025-07-19 update sch&pcb&step
2025-07-19 rm old files
2025-07-19 update chassis 3d
2025-08-01 update project
2025-08-01 add backups
2025-08-01 update chassis+sensor
2025-08-01 add ultrasonic stl
2025-08-02 update chassis, ultrasonic
2025-08-06 add motor assembly right stl
2025-08-06 add main project
2025-08-06 update main
2025-08-07 add gitignore
2025-08-07 remove fcbak
2025-08-10 add ultrasonic sensor support
2025-08-11 add crazy support
2025-08-11 add chassis
2025-08-11 add wheel
2025-08-11 add motor assembly
2025-08-11 add reforma tracking
2025-08-11 update wheel design
2025-08-14 add steps ruedas
2025-08-14 update crazy support
2025-08-14 update wheel
2025-08-19 add joystick v2
2025-08-20 add p5.js demo
2025-08-27 add reglamentos 2025
2025-08-27 update reglamentos
2025-08-27 add poster 2025
2025-09-08 update wheel, finish work
2025-09-08 update assembly project
2025-09-09 update main file
2025-09-29 update robotec repo
2025-10-01 rm files
2025-10-01 paper pid carreras
2025-11-05 add modalidad fútbol robot
2025-11-05 add tecnobot kits
2025-11-05 add DuinoBot info
2025-11-05 add duinobot v2.4 arduino lib
2025-11-08 micro automata v1
2025-11-08 add v2: node-red
2025-11-08 add v2 firmware
2025-11-08 add schematics
2025-11-16 add petri network draft
2025-11-16 add fsm drafts
2026-02-18 add LM567 datasheet
2026-02-18 add ULN200x datasheet
